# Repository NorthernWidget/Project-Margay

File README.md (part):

# Project-Margay

***Margay data logger v3.0.*** *Top side showing ATmega1284p processor, USB-C connector, screw terminal I/O on both sides, and LOG/STAT/RST buttons.*

Project Margay is a micro-scale environmental data logger based on the ALog series. It trades I/O capabilities for cost and size, resulting in a simple yet capable logger.

## Citation

If you use this data logger in a publication, please cite (temporary citation until a dedicated Margay paper is published):

**Wickert, A. D., K. R. Barnhart, W. H. Armstrong, M. Romero, B. Schulz, G.-H. C. Ng, C. T. Sandell, J. La Frenierre, S. B. Penprase, M. Van Wyk de Vries, and K. R. MacGregor (2024), [Automated ablation stakes to constrain temperature-index melt models](https://doi.org/10.1017/aog.2024.21), *Ann. Glaciol.*, *64*(92), 425–438, doi:10.1017/aog.2024.21.**

## Namesake

Due to its small size and adaptability to its environment, Project Margay owes its name to the small Margay cat native to the forests of Central and South America.

***A yawning margay cat***

## Technical Specifications

### Electronic Hardware
This includes a description of the PCB and component functionality

#### Features:
* ATMega1284p Processor
* 3.3v Logic
* On board full size SD card (for ease of field use)
* Extremely low sleep current
* Input voltage designed for use with easy to find alkaline batteries
* 0.1" Pitch headers can be populated with header pins and placed on a breadboard for prototyping

### Current iteration:

#### v3.0

***Margay data logger v3.0, back side.*** *Full-size SD card for data storage. US quarter (24.3 mm diameter) shown for scale.*

Changes from v2.2:
* USB-C connector (replacing micro-USB)
* Increased mounting hole sizes to fit #4 screws
* Moved one passive component to accommodate the larger holes

Input voltage: 3.5–5.5 V for regulated operation, 6.0 V absolute maximum; three alkaline AA or D cells (see [Battery voltage](#battery-voltage)). All other electrical specifications and pinout are identical to v2.2. Annotated pinout diagrams are in the [Pinout and board interfaces section below](#pinout-and-board-interfaces) and apply directly to v3.0.

### Past Iterations:

#### Features:
* ATMega644p Processor
* 3.3v Logic
* On board full size SD card (for ease of field use)
* Extremely low sleep current
* Input voltage designed for use with easy to find alkaline batteries
* 0.1" Pitch headers can be populated with header pins and placed on a breadboard for prototyping

#### v0.0 (Retired)
**Features** <br>
I<sub>Q</sub> = 1.6mA <br>
I<sub>out</sub> = 50mA, max (Regulated power supplied to sensors) <br>
V<sub>in</sub> = 3.3 ~ 5.5v <br>

**IO**:
* 1 I2C Bus
* 1 SPI Bus, with up to 2 CS pins
* 1 PWM Channel (output configurable to 3.3v or VBat via a jumper on bottom of board)
* RGB Status LED
* Auxiliary LED
* Reset Button
* Reconfigurable Button

#### v1.0
**Features** <br>
I<sub>Q</sub> = 2.5&mu;A <br>
I<sub>out</sub> = 50mA, max (Regulated power supplied to sensors) <br>
V<sub>in</sub> = 3.3 ~ 5.5v (Reverse polarity protected) <br>

**IO**
* 1 ADC, 18 bit
* 1 I<sup>2</sup>C Bus
* 1 SPI Bus, with up to 2 CS pins
* 1 PWM Channel (output configurable to 3.3v or VBat via a jumper on bottom of board)
* RGB Status LED
* Auxiliary LED
* Reset Button
* Reconfigurable Button

#### v2.0
**Features** <br>
I<sub>Q</sub> = <2.5&mu;A (Estimated) <br>
I<sub>out</sub> = 200mA, max (Regulated power supplied to sensors) <br>
V<sub>in</sub> = 3.3 ~ 5.5v (Reverse polarity protected) <br>

**IO**
* 1 ADC, 18 bit
* 1 I<sup>2</sup>C Bus
* 1 UART Channel
* 2 GPIO Pins (one configurable as an 8 bit ADC)
* 1 PWM Channel (output configurable to 3.3v or VBat via a jumper on bottom of board)
* RGB Status LED
* Auxiliary LED
* Reset Button
* Reconfigurable Button

#### v2.2
**Features** <br>
I<sub>Q</sub> = 1.68&mu;A <br>
I<sub>out</sub> = 200mA, max (Regulated power supplied to sensors) <br>
V<sub>in</sub> = 3.3 ~ 5.5v (Reverse polarity protected) <br>

**IO**
* 1 ADC, 18 bit
* 1 I<sup>2</sup>C Bus
* 1 UART Channel
* 2 GPIO Pins (one configurable as an 8 bit ADC)
* 1 PWM Channel (output configurable to 3.3v or VBat via a jumper on bottom of board)
* RGB Status LED
* Auxiliary LED
* Reset Button
* Reconfigurable Button

### Electronic Software and Firmware

* Programmable using the Arduino IDE https://www.arduino.cc/en/software
* Custom bootloader and board definition for ATMega1284p available via https://github.com/NorthernWidget/Arduino_Boards
* Custom libraries from Northern Widget and the open-source community
  * Primary data-logger functions
  * Libraries available with each sensor, exposing a standard interface
* Open-source licensing via GNU GPL 3.0

### Pinout and board interfaces
Pinout is listed on bottom of board. The pinout is identical across v2.2 and v3.0.

***Margay data logger with pins, connectors, and interactive items annotated, top side.***

**Pins are colored following this convention:**
* Ground: black
* Positive voltage: red
* Universal Serial Asynchronous Receiver--Transmitter (UART or USART) bus: blue
* Digital I/O: gray
* Analog measurement system: green
* I2C bus: purple

*The jumper on the front of the board, to the right of "B+" and "Ax", connects an on-board reference resistor (10 kOhm in our builds) with the analog pin Ax to create a voltage divider in which the sensor between Ax and REF is on the GND side of the voltage divider.*

***Margay data logger annotated, bottom side.*** This is where the labels for the above pins are printed.

In this pinout, the name of each pin is shown, as well as the group of pins which it belongs to, a detailed description of the pins and callouts follows:

#### Pins:
* 3v3, the switched 3.3v output rail, this rail can be turned on and off to disconnect power consumptive external devices
* GND, the main output ground
* BAT+, the positive connection for the battery line: 3.5–5.5 V for regulated operation, 6.0 V absolute maximum (see [Battery voltage](#battery-voltage) for the limits and the cells to use)
* BAT-, Negative battery connection, ***note: this pin is NOT interchangeable with GND, as BAT- is reverse voltage protected to prevent damage from plugging the battery in backwards***
* Vs, this is the switched PWM output, the voltage of this output is determined by a solder jumper on the bottom of the board, controlled by `VSwitch_Pin` - See information of limits and configuration below

* MOSI, this is the master out, slave in, pin for the SPI bus, which doubles as **D5** when SPI and SD card are not used
* MISO, this is the master in, slave out, pin for the SPI bus, which doubles as **D6** when SPI and SD card are not used
* SCK, this is the clock line for the SPI bus, which doubles as **D7** when SPI and SD card are not used
* CS, this is the chip select pin for the SPI bus, which doubles as both **D11** and **INT1** when external SPI is not used (Can be used even when SD card is used)

* SCL, this is the dedicated serial clock line for the I2C bus
* SDA, this is the dedicated serial data line for the I2C bus

#### Callouts:
1. This is the auxiliary LED, which indicate TX and RX status using red and blue channels, green channel is controlled by `BuiltInLED` pin
2. This is the USB connection (USB-C on v3.0; micro-USB on v2.x), which can be used for both programming via the Arduino IDE and serial monitoring
3. This is the primary RGB status LED, where the individual channels are controlled by **D15**, **D14**, and **D13**
4. This is the reconfigurable push-button, generally used to initiate logging, it is read by `LogInt` pin
5. This is the hardware reset button, which will force the micro to return to the initial state after code upload
6. This is the ICSP header, which can be used to burn the bootloader to the board or write programs to the chip without using the USB and bootloader

#### Onboard Pins:
Pin Name | Pin Number (v0.0) | Pin Number (v1.0) | Pin Number (v2.x) | Function
-------- | ----------------- | ----------------- | ----------------- | --------
`SD_CS` | D4 | D4 | D4 | Chip select pin on SD card
`SD_CD` | D1 | D1 | D1 | Card detection pin for SD card, active low, AUX power must be on to use
`BuiltInLED` | D19 | D20 | D20 | Connected to green channel on **AUX** LED, on when pin is low
`RedLED` | D13 | D13 | D13 | Connected to red channel on **STAT** LED, on when pin is low
`GreenLED` | D15 | D15 | D15 | Connected to green channel on **STAT** LED, on when pin is low
`BlueLED` | D14 | D14 | D14 | Connected to blue channel on **STAT** LED, on when pin is low
`VRef_Pin` | A2 | A2 | A3 | Analog pin to read 1.8v on board reference, AUX power must be on to use
`BatSensePin` | A0 | A0 | A2 | Analog pin to read battery voltage divider, AUX power must be on to use
`VSwitch_Pin` | D3 | D3 | D12 | Connected to MOSFET driver for **Vs** pin, active low
`Ext3v3Ctrl` | D12 | D19 | D22 | Turns on AUX power, active low
`I2C_SW` | N/A | D12 | D21 | Switches between on board I2C and external I2C
`PG` | D18 | D18 | D18 | Power good pin from core 3v3, can be used to test if core 3v3 is stable, pulled low when power is not stable
`ExtInt` | D11 | D11 | D11 | External interrupt and external chip select pin
`RTCInt` | D10 | D10 | D2 | Interrupt connected to RTC /INT line, active low
`LogInt` | D2 | D2 | A4 | Interrupt connected to **LOG** button, active low

#### VSwitch Power Limits/Configuration:
Jumper Selected | Logger Power Source | Current Limit, Avg [mA] | Power Limit, Avg [W] | Set by
--------------- | ------------------- | ---------------------- | -------------------- | ------
VMain | USB | 100 | 0.5 | TPS2104, USB input (IN2)<sup>1</sup>
VMain | Bat | 500 | 2.25 | TPS2104, battery input (IN1)
3v3 | USB | 100 | 0.33 | TPS2104, USB input (IN2)<sup>1</sup>
3v3 | Bat | 200 | 0.66 | TPS7A05, shared with the SD card and on-board sensors

<sup>1</sup> <small>Rated continuous current. The TPS2104 can deliver up to 220 mA here, with a larger voltage drop.</small>

Note: Instantaneous current may exceed these values — these values correspond to the time-averaged power consumption. This distinction is most important when driving a load via PWM.

#### Battery voltage

Use three alkaline cells in series, AA or D. A fresh pack reads about 4.8 V (1.56–1.65 V per cell) and runs the logger for the life of the cells.

| Limit | Voltage | Set by |
|---|---|---|
| Absolute maximum | 6.0 V | every chip on the battery line: TPS79733 (core regulator), TPS22916 (battery switch), TPS2104 (USB/battery switch), TPS7A05 (switched 3.3 V regulator) and MIC94090 (Vs switch, with the jumper on its default side) |
| Maximum for operation | 5.5 V | the same chips |
| Core 3.3 V in regulation down to | 3.5 V | the TPS79733's dropout (200 mV maximum at 10 mA) |
| Switched 3.3 V in regulation at its full 200 mA down to | 3.63 V | the TPS7A05's dropout plus the switches ahead of it |

Below these, the 3.3 V rails follow the battery down. The logger reports a battery under 3.3 V as too low to work properly (red, fast blinking).

Do not use:
* **Lithium AA cells** (lithium iron disulfide, such as Energizer Ultimate Lithium). Three fresh cells read 5.37–5.49 V, within 0.13 V of the 5.5 V maximum.
* **3.6 V lithium AA-size cells** (lithium thionyl chloride, such as Saft LS14500). Three in series reach about 11 V and will destroy the logger.

NiMH cells (about 3.75–4.26 V for three) work, but leave only about 0.1 V of headroom for the switched 3.3 V rail at full load.

On USB, use a standard 5 V port or charger. The FT231X USB chip sets the ceiling there: its absolute maximum is 5.5 V, behind one Schottky diode.

## On-board Devices

### I2C

| **Device**                                                	| **Default address** 	| **Reprogrammable address** 	| **Function**                                                     	|
|-----------------------------------------------------------	|---------------------	|----------------------------	|------------------------------------------------------------------	|
| [DS3231](https://github.com/NorthernWidget/DS3231_Logger) 	| 0x68                	| N                          	| Real-time clock                                                  	|
| [MCP3421](https://github.com/NorthernWidget/MCP3421)      	| 0x6A                	| N                          	| ADC                                                              	|
| [BME280](https://github.com/NorthernWidget/BME_Library)   	| 0x77                	| N                          	| On-board barometric pressure, temperature, and relative humidity 	|

### SPI

* SD Card

### UART (USART)

* FTDI USB-Serial converter

## Assembly

Assembling this data logger is possible by hand with sufficient skill and the following tools:
* Temperature-controlled soldering iron
* Hot-air rework station
* Equipment for stenciling with solder paste
* ESD-safe tweezers and workstation
* Solder wick

Mechanized assembly by a professional circuit-board assembly house, which is available in many parts of the world, may be preferred due to the complexity of this data logger board.

## Programming

### Downloading and installing the Arduino IDE

Go to https://www.arduino.cc/en/software and download the IDE for your operating system. The web editor does not support custom libraries and will not work for this project. Install the IDE and open it before continuing.

For additional setup guidance, see the [Northern Widget tutorial](https://docs.northernwidget.com/tutorial/).

### Installing the bootloader

Before a data logger can receive programs via USB, it must have a *bootloader* installed. You can read more about bootloaders here: https://www.arduino.cc/en/Hacking/Bootloader.

The bootloader is loaded via the 6-pin ICSP (ISP) header using an in-circuit system programmer. Many programmers work:
* The official [AVR ISP mkII](http://ww1.microchip.com/downloads/en/DeviceDoc/Atmel-42093-AVR-ISP-mkII_UserGuide.pdf) (no longer produced but available used)
* Using an [Arduino as an ISP](https://www.arduino.cc/en/tutorial/arduinoISP)
* The versatile [Olimex AVR-ISP-MK2](https://www.olimex.com/Products/AVR/Programmers/AVR-ISP-MK2/open-source-hardware)
* The [Adafruit USBtinyISP](https://www.adafruit.com/product/46)

***Important note for Linux users:*** You must supply permissions to the Arduino IDE for it to use the ICSP, or run the IDE with `sudo`.

To install the bootloader:

1. Open the Arduino IDE and install the Northern Widget board definitions: https://github.com/NorthernWidget/Arduino_Boards — the Margay uses the **TLog v1** definition.
2. Select ***ATMega1284p 8MHz*** under *Tools → Board → Northern Widget Boards*.
3. Plug the Margay into your computer via USB (USB-C on v3.0; micro-USB on v2.x) to power it.
4. Plug your ISP into your computer and onto the 6-pin ICSP header. The ribbon cable should face away from the board; if programming fails, try flipping the connector.
5. Go to *Tools → Programmer* and select your programmer.
6. Go to *Tools → Burn Bootloader*. Within a few seconds you will see a success or failure message.

***Note: Download and install drivers for your ISP before use.***

### Hardware test sketch

The [`MargaySetup`](Software/MargaySetup/MargaySetup.ino) sketch verifies every hardware subsystem over the serial monitor at 38400 baud. It also handles serial number programming (`SN Set` / `SN Read`). See the [Full hardware test command reference](#full-hardware-test-command-reference) table below.

Install these libraries before uploading (see [Arduino manual install guide](https://www.arduino.cc/en/Guide/Libraries)):
* [DS3231](https://github.com/NorthernWidget/DS3231) — real-time clock
* [MCP3421](https://github.com/NorthernWidget/MCP3421) — on-board ADC
* SD — bundled with the Arduino IDE

### Data logging

For data logging, use the [Margay_Library](https://github.com/NorthernWidget/Margay_Library). It manages sleep/wake, SD writes, RTC reads, and on-board sensor sampling automatically. See the [Sample code](#sample-code) section below.

Install these libraries manually from GitHub (see [Arduino manual install guide](https://www.arduino.cc/en/Guide/Libraries)):
* [Margay_Library](https://github.com/NorthernWidget/Margay_Library)
* [DS3231_Logger](https://github.com/NorthernWidget/DS3231_Logger)
* [NW_MCP3421](https://github.com/NorthernWidget/MCP3421)
* [BME](https://github.com/NorthernWidget/BME_Library)
* [SdFat](https://github.com/greiman/SdFat) — available via *Tools → Manage Libraries*

### Setting the serial number

Upload the [MargaySetup](Software/MargaySetup/MargaySetup.ino) sketch, open the serial monitor at **38400 baud**, and type `SN Set` followed by a carriage return or newline. You will be prompted for three 4-digit hexadecimal fields:
* **Board type:** `0x4D03` for Margay v3.0; `0x4D02` for v2.2 (full series: v0.0 = `0x4D00`, v1.0 = `0x4D01`). If you built your own board, do not use these codes — they are reserved for Northern Widget recordkeeping.
* **Group ID:** Used to denote collaborative projects vs. internal use vs. general sales.
* **Unique ID:** A monotonically increasing number.

To read back the serial number, type `SN Read`.

### Full hardware test command reference

The same sketch provides a serial command interface at **38400 baud** for testing all individual hardware subsystems. Send a command followed by a carriage return or newline. Continuous tests run until a carriage return is sent to stop them.

Command | Description
--------|------------
`SD` | Writes a random value and short string to the SD card, reads it back, reports PASS/FAIL
`Clock` | Sets the RTC to a known time, waits 5 seconds, reads it back, reports PASS/FAIL
`I2C` | Scans the I2C bus and prints the address of every device found
`ADC Disp` | Continuously prints voltages for the on-board reference, thermistor, battery, and external ADC (Ax)
`IO` | Toggles the VSwitch and ExtInt pins
`PG` | Reads the Power Good pin and reports PASS/FAIL
`Power` | Toggles the external 3.3V rail on and off
`Button` | Waits 2 seconds for the Log button to be pressed and reports if detected
`LED` | Cycles through each channel of the RGB and AUX LEDs
`SN Set` | Sets the serial number in EEPROM (see above)
`SN Read` | Reads back the serial number from EEPROM

### Using Custom Software (Developer)
As we provide all information about on board pins and their functionality, it is easy for a user to write their own code in the Arduino IDE to leverage the hardware capabilities of the Margay to whatever degree is desired. To do this, the Northern Widget board file can be used (as described above), or the **[MightyCore](https://github.com/MCUdude/MightyCore)** board files can be used. These are the board files the Northern Widget ones were based on, but allow for more compilation options for the user. Full instructions for installation and use are provided on the MightyCore GitHub page.

For **v2.0 and later** (ATmega1284p), the recommended settings are:

Setting | Value
--------|------
`Board` | `ATmega1284`
`Pinout` | `Standard`
`Clock` | `8MHz External`
`Compiler LTO` | `Disabled`
`Variant` | `1284P`
`BOD` | `2.7v`

For **v0.0 and v1.0** (ATmega644p), the recommended settings are:

Setting | Value
--------|------
`Board` | `ATmega644`
`Pinout` | `Standard`
`Clock` | `8MHz External`
`Compiler LTO` | `Disabled`
`Variant` | `644P / 644PA`
`BOD` | `2.7v`

#### Sample code

`Margay_NoSensors.ino`

```c++
#include "Margay.h"
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
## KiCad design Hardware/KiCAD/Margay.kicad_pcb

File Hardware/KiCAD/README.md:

# Hardware/Margay_2 — Eagle-to-KiCAD port, current working version (work in progress)

This is the most current KiCAD design for the Margay v3.0, representing the active Eagle-to-KiCAD port.

**Current state:** schematic is split across three hierarchical sheets (`Margay_1/2/3.kicad_sch`) imported from Eagle; every symbol and footprint now comes from the shared `nw-cold-silicon` library, and the importer's `Margay-eagle-import.kicad_sym` and `Margay.pretty` have been retired. PCB layout (`Margay.kicad_pcb`) is also present. Both are works in progress and have not been verified against the v3.0 production Gerbers.

Tracking issue: https://github.com/NorthernWidget/Project-Margay/issues/41

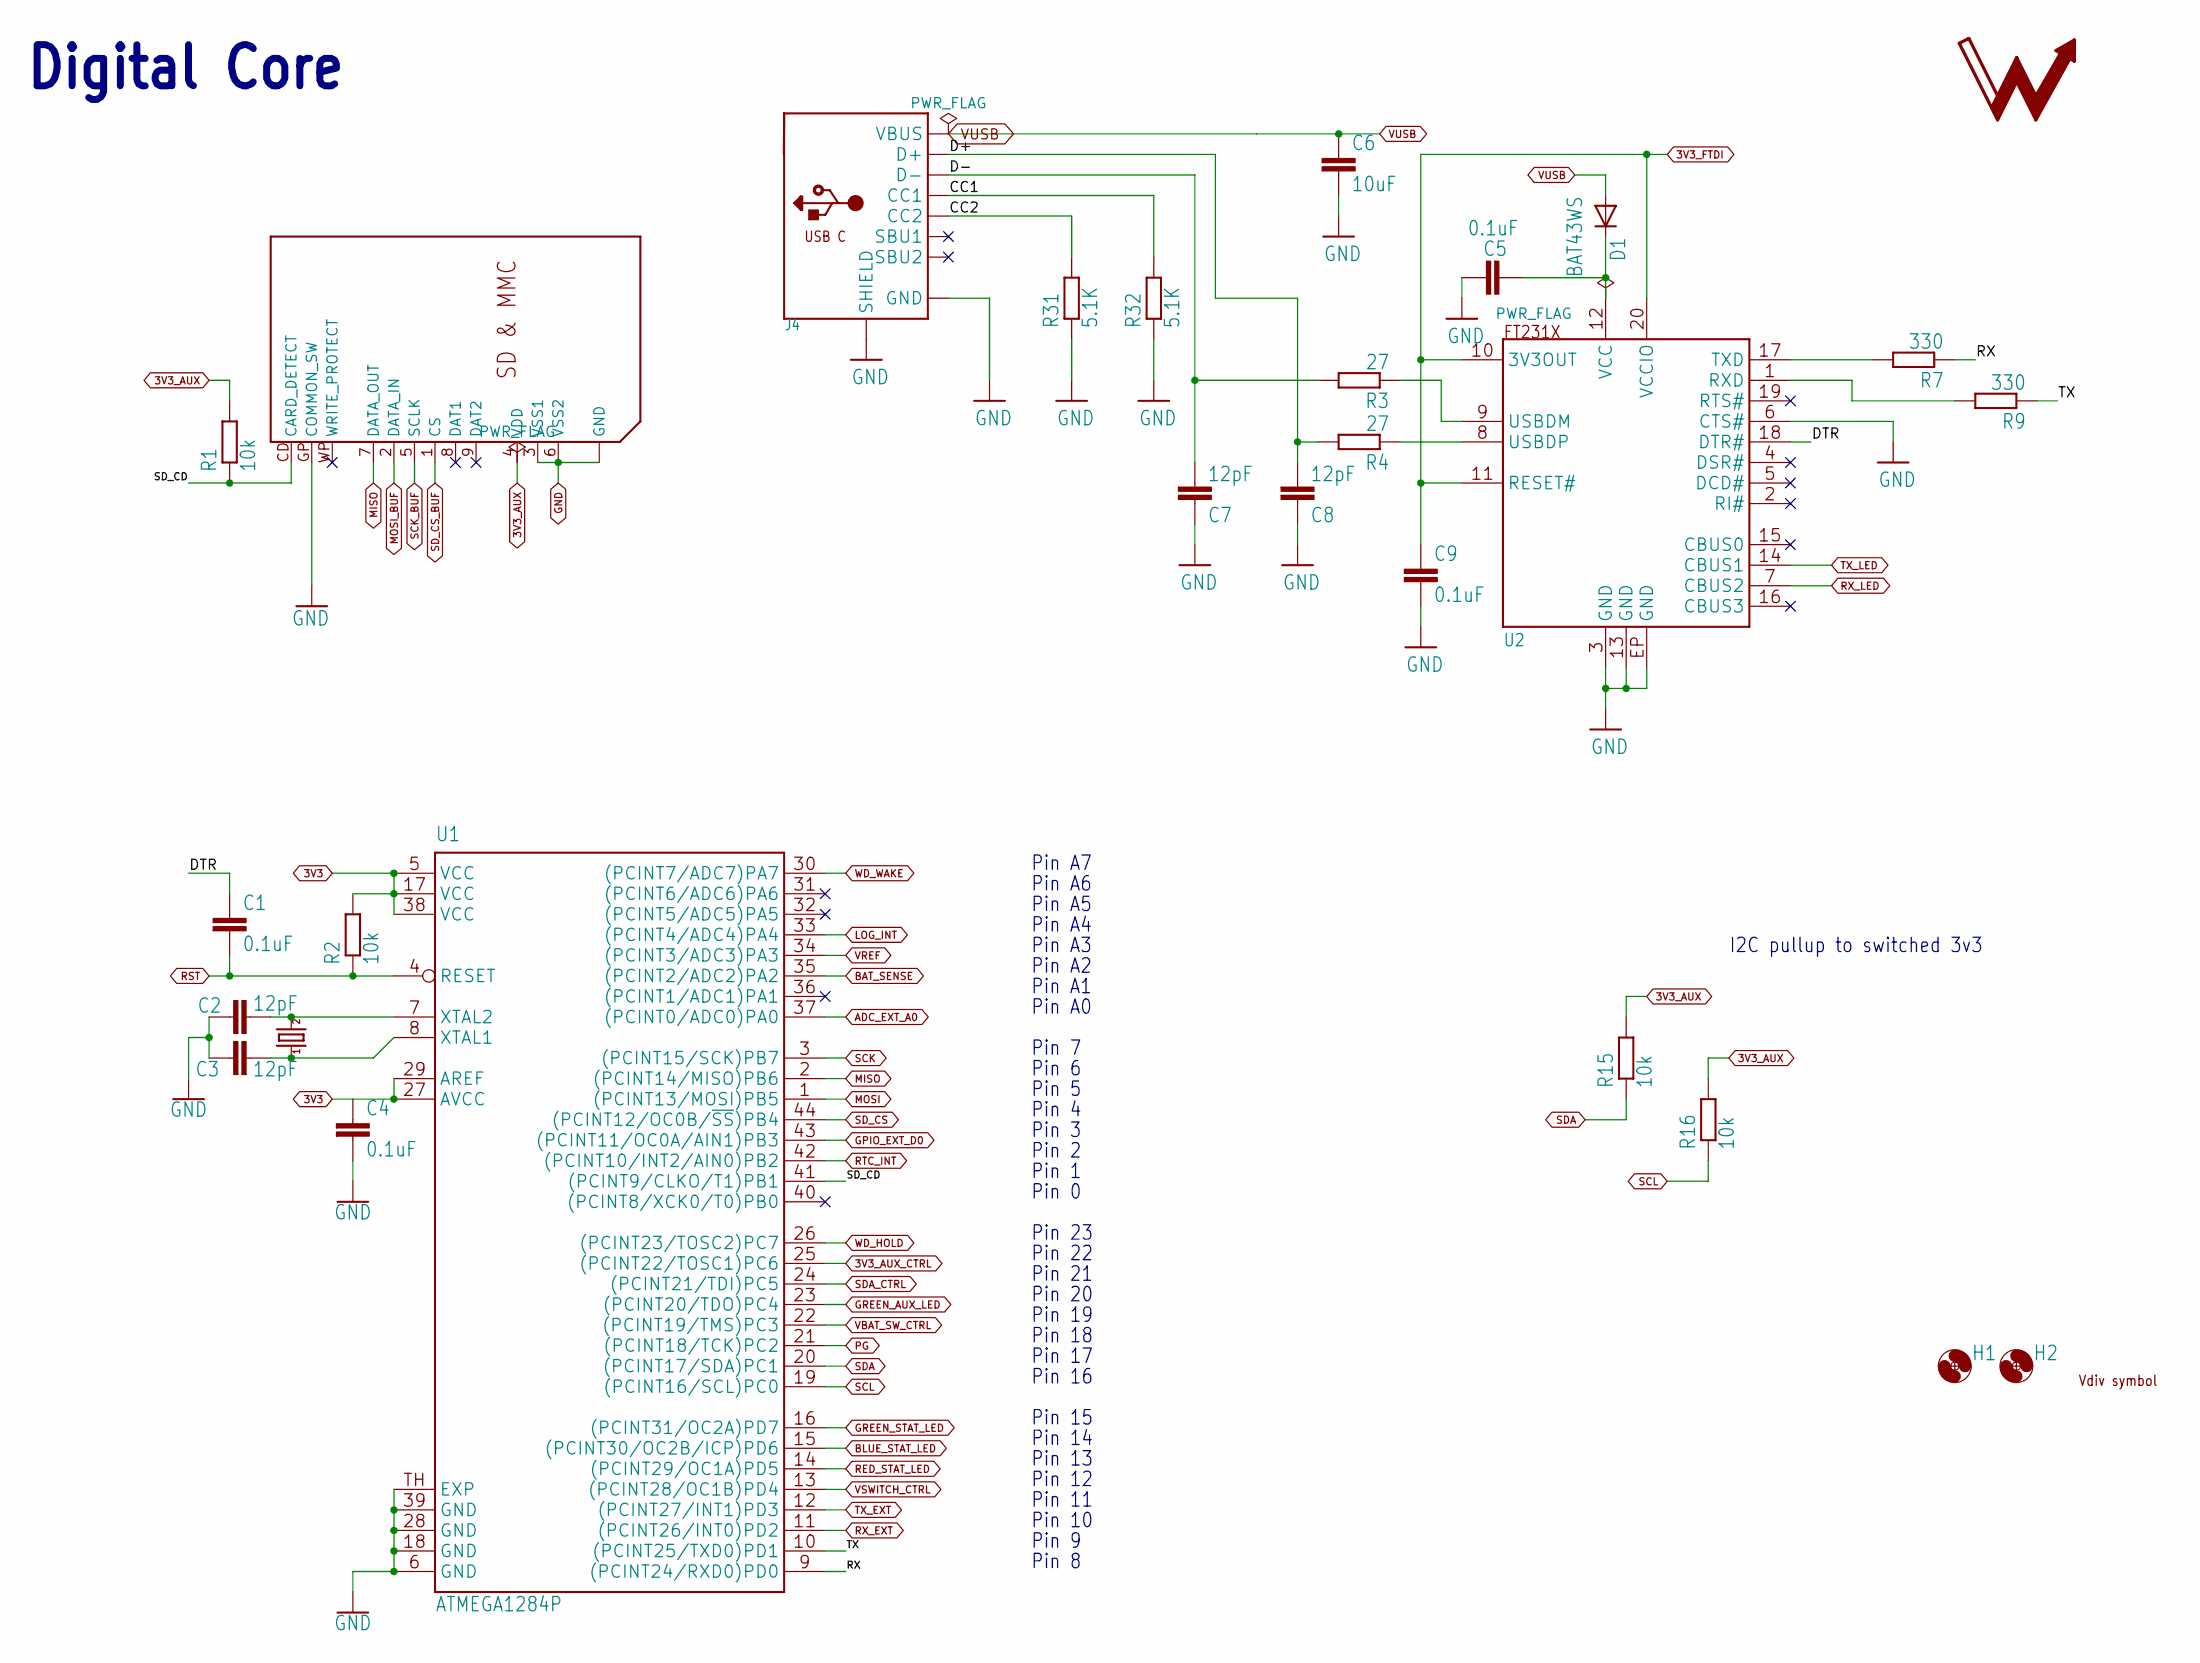
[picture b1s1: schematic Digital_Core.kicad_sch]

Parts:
C1, C4, C5, C9: 0.1uF; C0402; MPN GCM155R71C104KA55D; DIGIKEY 490-4759-1-ND
C2, C3, C7, C8: 12pF; C0402; MPN CGA2B2C0G1H120J050BA; DIGIKEY 445-5585-1-ND
C6: 10uF; C0805; MPN GRM21BR61C106KE15K; DIGIKEY 490-6473-1-ND
D1: BAT43WS; SOD323-R; MPN BAT43WS-HE3_A-08; DIGIKEY 112-BAT43WS-HE3_A-08CT-ND
H1, H2: MOUNTING_HOLE4_NP_CLOSE; 4_40_CLOSE; MPN N/A; DIGIKEY DNP
J1: SDMMCWR-CRD; SD_WURTH_WR-CRD; MPN 693063010911; DIGIKEY 732-3817-1-ND
J4: USB_C; USB_C_CUSB31-CFM2AX-01-X; MPN USB4105-GF-A; DIGIKEY 2073-USB4105-GF-ACT-ND
LOGO1: NWLOGO_MED
R1, R2, R15, R16: 10k; R0402; MPN ERJ-2RKF1002X; DIGIKEY P10.0KLCT-ND
R3, R4: 27; R0402; MPN ERJ-2RKF27R0X; DIGIKEY P27.0LCT-ND
R7, R9: 330; R0402; MPN ERJ-2RKF3300X; DIGIKEY P330LCT-ND
R31, R32: 5.1K; R0402; MPN ERJ-2RKF5101X; DIGIKEY P5.10KLCT-ND
U1: ATMEGA1284P; MLF44-TH; MPN ATMEGA1284P-MU; DIGIKEY ATMEGA1284P-MU-ND
U2: FT231X-Q; QFN20; MPN FT231XQ-R; DIGIKEY 768-1128-1-ND
U$1: VDIV_MARGAYFULL-VDIV; VDIV_MARGAY_2026; MPN N/A; DIGIKEY DNP
XTAL1: CRYSTAL5X3.2; CRYSTAL_5X3.2_2-SMD; MPN ECS-80-12-30-JGN-TR; DIGIKEY 50-ECS-80-12-30-JGN-CT-ND

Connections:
3V3: C4.1, R2.2, U1.5 (VCC), U1.17 (VCC), U1.27 (AVCC), U1.29 (AREF), U1.38 (VCC); also elsewhere on the board
3V3_AUX: J1.4 (VDD), R1.2, R15.2, R16.2; also elsewhere on the board
3V3_AUX_CTRL: U1.25 ((PCINT22/TOSC1)PC6); also elsewhere on the board
3V3_FTDI: C9.1, U2.10 (3V3OUT), U2.11 (RESET#), U2.20 (VCCIO); also elsewhere on the board
/Digital_Core/CC1: J4.A5 (CC1), R32.2
/Digital_Core/CC2: J4.B5 (CC2), R31.2
/Digital_Core/D+: C8.2, J4.A6 (D+), J4.B6 (D+), R4.2
/Digital_Core/D-: C7.2, J4.A7 (D-), J4.B7 (D-), R3.2
/Digital_Core/DTR: C1.1, U2.18 (DTR#)
/Digital_Core/RX: R7.1, U1.9 ((PCINT24/RXD0)PD0)
/Digital_Core/SD_CD: J1.CD (CARD_DETECT), R1.1, U1.41 ((PCINT9/CLKO/T1)PB1)
/Digital_Core/TX: R9.1, U1.10 ((PCINT25/TXD0)PD1)
ADC_EXT_A0: U1.37 ((PCINT0/ADC0)PA0); also elsewhere on the board
BAT_SENSE: U1.35 ((PCINT2/ADC2)PA2); also elsewhere on the board
BLUE_STAT_LED: U1.15 ((PCINT30/OC2B/ICP)PD6); also elsewhere on the board
GND: C2.1, C3.1, C4.2, C5.2, C6.2, C7.1, C8.1, C9.2, J1.3 (VSS1), J1.6 (VSS2), J1.GP (COMMON_SW), J1.GP2 (GND), J1.GP3 (GND), J1.GP4 (GND), J4.A1B12 (GND), J4.B1A12 (GND), J4.S1 (SHIELD), R31.1, R32.1, U1.6 (GND), U1.18 (GND), U1.28 (GND), U1.39 (GND), U1.TH (EXP), U2.3 (GND), U2.6 (CTS#), U2.13 (GND), U2.EP (GND); also elsewhere on the board
GPIO_EXT_D0: U1.43 ((PCINT11/OC0A/AIN1)PB3); also elsewhere on the board
GREEN_AUX_LED: U1.23 ((PCINT20/TDO)PC4); also elsewhere on the board
GREEN_STAT_LED: U1.16 ((PCINT31/OC2A)PD7); also elsewhere on the board
LOG_INT: U1.33 ((PCINT4/ADC4)PA4); also elsewhere on the board
MISO: J1.7 (DATA_OUT), U1.2 ((PCINT14/MISO)PB6); also elsewhere on the board
MOSI: U1.1 ((PCINT13/MOSI)PB5); also elsewhere on the board
MOSI_BUF: J1.2 (DATA_IN); also elsewhere on the board
unnamed: C3.2, U1.8 (XTAL1), XTAL1.OSC1 (1)
unnamed: C2.2, U1.7 (XTAL2), XTAL1.OSC2 (2)
unnamed: R9.2, U2.1 (RXD)
unnamed: R7.2, U2.17 (TXD)
unnamed: R3.1, U2.9 (USBDM)
unnamed: R4.1, U2.8 (USBDP)
PG: U1.21 ((PCINT18/TCK)PC2); also elsewhere on the board
RED_STAT_LED: U1.14 ((PCINT29/OC1A)PD5); also elsewhere on the board
RST: C1.2, R2.1, U1.4 (RESET); also elsewhere on the board
RTC_INT: U1.42 ((PCINT10/INT2/AIN0)PB2); also elsewhere on the board
RX_EXT: U1.11 ((PCINT26/INT0)PD2); also elsewhere on the board
RX_LED: U2.7 (CBUS2); also elsewhere on the board
SCK: U1.3 ((PCINT15/SCK)PB7); also elsewhere on the board
SCK_BUF: J1.5 (SCLK); also elsewhere on the board
SCL: R16.1, U1.19 ((PCINT16/SCL)PC0); also elsewhere on the board
SDA: R15.1, U1.20 ((PCINT17/SDA)PC1); also elsewhere on the board
SDA_CTRL: U1.24 ((PCINT21/TDI)PC5); also elsewhere on the board
SD_CS: U1.44 ((PCINT12/OC0B/~SS)PB4); also elsewhere on the board
SD_CS_BUF: J1.1 (CS); also elsewhere on the board
TX_EXT: U1.12 ((PCINT27/INT1)PD3); also elsewhere on the board
TX_LED: U2.14 (CBUS1); also elsewhere on the board
VBAT_SW_CTRL: U1.22 ((PCINT19/TMS)PC3); also elsewhere on the board
VREF: U1.34 ((PCINT3/ADC3)PA3); also elsewhere on the board
VSWITCH_CTRL: U1.13 ((PCINT28/OC1B)PD4); also elsewhere on the board
WD_HOLD: U1.26 ((PCINT23/TOSC2)PC7); also elsewhere on the board

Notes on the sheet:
Pin A2
Pin 13
Pin 23
Pin A7
Pin 20
Pin 6
Pin 16
Pin 17
Pin 5
Pin 12
Pin 14
Pin 9
Pin 0
Pin 4
Pin 10
Pin 22
Pin 8
Pin A6
Pin 7
Pin A4
Pin 15
Digital Core
Pin 3
Pin A1
Pin 18
Pin A0
Pin 19
Pin 1
Pin 21
I2C pullup to switched 3v3
Pin A3
Pin A5
Pin 11
Pin 2

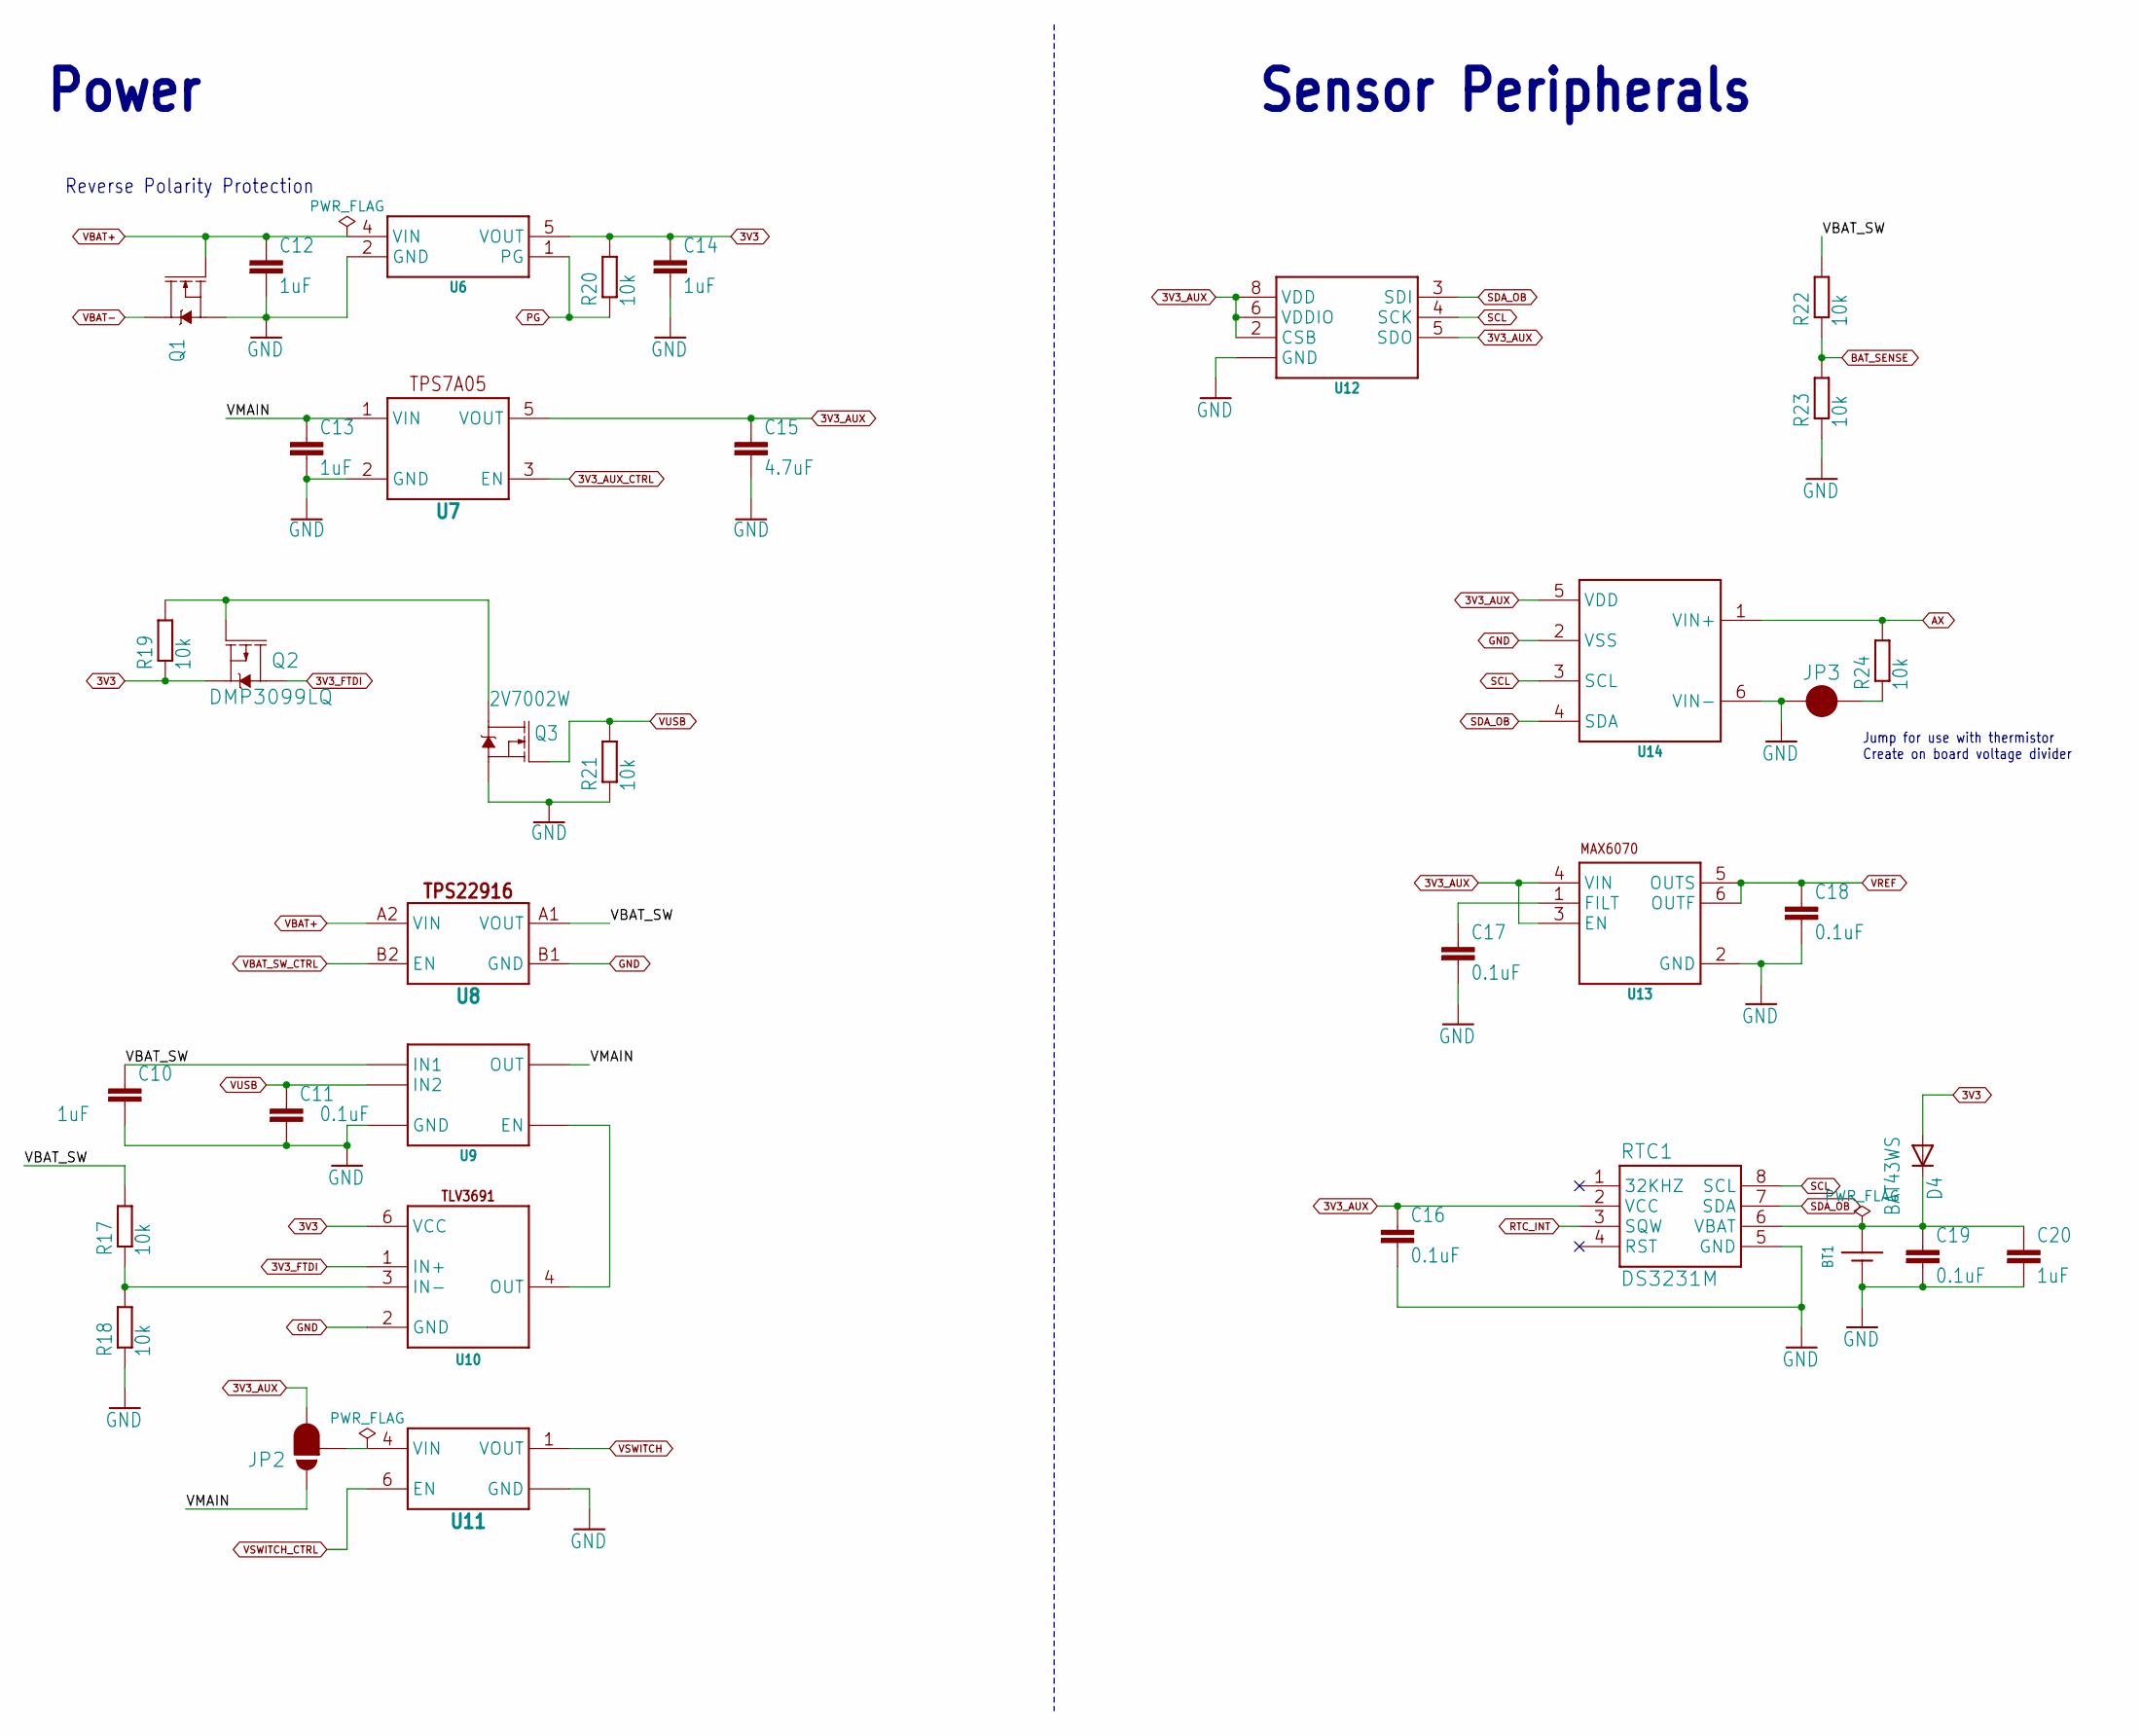
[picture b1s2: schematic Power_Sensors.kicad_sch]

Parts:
BT1: BATTERY_COIN12MM; LINX_BAT-HLD-012-SMT; MPN BK-916-TR; DIGIKEY BK-916-CT-ND
C10, C12, C13, C14, C20: 1uF; C0603; MPN GCM188R71E105KA64D; DIGIKEY 490-10673-1-ND
C11, C16, C17, C18, C19: 0.1uF; C0402; MPN GCM155R71C104KA55D; DIGIKEY 490-4759-1-ND
C15: 4.7uF; C0603; MPN GRT188R61C475KE13J; DIGIKEY 490-GRT188R61C475KE13JCT-ND
D4: BAT43WS; SOD323-R; MPN BAT43WS-HE3_A-08; DIGIKEY 112-BAT43WS-HE3_A-08CT-ND
JP2: JUMPER-SMT_3_1-NC_PASTE_SILK; SMT-JUMPER_3_1-NC_PASTE_SILK; MPN N/A; DIGIKEY DNP
JP3: JUMPER-SMT_2_NC_PASTE_SILK; SMT-JUMPER_2_NC_PASTE_SILK; MPN N/A; DIGIKEY DNP
Q1: MOSFET-NCH-DMG3404L; SOT23-3; MPN DMG3404L-7; DIGIKEY DMG3404L-7DICT-ND
Q2: DMP3099LQ; SOT23-3; MPN DMP3099LQ-7; DIGIKEY 31-DMP3099LQ-7CT-ND
Q3: 2V7002W; SOT323; MPN 2V7002WT1G; DIGIKEY 2V7002WT1GOSCT-ND
R17, R18, R19, R20, R21: 10k; R0402; MPN ERJ-2RKF1002X; DIGIKEY P10.0KLCT-ND
R22, R23, R24: 10k; R0603; MPN RG1608P-103-B-T5; DIGIKEY RG16P10.0KBCT-ND
RTC1: DS3231M; SO08; MPN DS3231MZ+; DIGIKEY DS3231MZ+-ND
U6: TPS797; DCK_R-PDSO-G5; MPN TPS79733DCKR; DIGIKEY 296-11990-1-ND
U7: TPS7A05DBV; SOT23-5; MPN TPS7A0533PDBVR; DIGIKEY 296-TPS7A0533PDBVRCT-ND
U8: TPS22916YFP; YFP0004; MPN TPS22916CYFPT; DIGIKEY 296-47464-1-ND
U9: TPS210; SOT23-5; MPN TPS2104DBVT; DIGIKEY 296-TPS2104DBVTCT-ND
U10: TLV3691DPF; DPF0006A; MPN TLV3691IDPFR; DIGIKEY 296-37242-6-ND
U11: MIC9409C6; SC-70_6; MPN MIC94090YC6-TR; DIGIKEY 576-3484-1-ND
U12: BME280; MPN BME280; DIGIKEY 828-1063-1-ND
U13: MAX6070BAUT18; SOT23-6L; MPN MAX6070BAUT18+T; DIGIKEY MAX6070BAUT18+TCT-ND
U14: MCP342; SOT23-6L; MPN MCP3421A1T-E/CH; DIGIKEY MCP3421A1T-E/CHCT-ND

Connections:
3V3: C14.1, D4.A, Q2.2 (S), R19.1, R20.2, U6.5 (VOUT), U10.6 (VCC); also elsewhere on the board
3V3_AUX: C15.1, C16.1, JP2.3, RTC1.2 (VCC), U7.5 (VOUT), U12.2 (CSB), U12.5 (SDO), U12.6 (VDDIO), U12.8 (VDD), U13.3 (EN), U13.4 (VIN), U14.5 (VDD); also elsewhere on the board
3V3_AUX_CTRL: U7.3 (EN); also elsewhere on the board
3V3_FTDI: Q2.3 (D), U10.1 (IN+); also elsewhere on the board
/Power_Sensors/VBAT_SW: C10.1, R17.2, R22.2, U8.A1 (VOUT), U9.5 (IN1)
/Power_Sensors/VMAIN: C13.1, JP2.1, U7.1 (VIN), U9.4 (OUT)
AX: R24.2, U14.1 (VIN+); also elsewhere on the board
BAT_SENSE: R22.1, R23.2; also elsewhere on the board
GND: BT1.GND (-), C10.2, C11.2, C12.2, C13.2, C14.2, C15.2, C16.2, C17.2, C18.2, C19.2, C20.2, JP3.1, Q1.2 (S), Q3.2 (S), R18.1, R21.1, R23.1, RTC1.5 (GND), U6.2 (GND), U7.2 (GND), U8.B1 (GND), U9.2 (GND), U10.2 (GND), U11.2 (GND), U11.5 (GND), U12.1 (GND), U12.7 (GND), U13.2 (GND), U14.2 (VSS), U14.6 (VIN-); also elsewhere on the board
unnamed: BT1.POWER0 (+), C19.1, C20.1, D4.C, RTC1.6 (VBAT)
unnamed: JP3.2, R24.1
unnamed: Q2.1 (G), Q3.3 (D), R19.2
unnamed: R17.1, R18.2, U10.3 (IN-)
unnamed: U9.1 (EN), U10.4 (OUT)
unnamed: JP2.2, U11.4 (VIN)
unnamed: C17.1, U13.1 (FILT)
PG: R20.1, U6.1 (PG); also elsewhere on the board
RTC_INT: RTC1.3 (SQW); also elsewhere on the board
SCL: RTC1.8 (SCL), U12.4 (SCK), U14.3 (SCL); also elsewhere on the board
SDA_OB: RTC1.7 (SDA), U12.3 (SDI), U14.4 (SDA); also elsewhere on the board
VBAT+: C12.1, Q1.1 (G), U6.4 (VIN), U8.A2 (VIN); also elsewhere on the board
VBAT-: Q1.3 (D); also elsewhere on the board
VBAT_SW_CTRL: U8.B2 (EN); also elsewhere on the board
VREF: C18.1, U13.5 (OUTS), U13.6 (OUTF); also elsewhere on the board
VSWITCH: U11.1 (VOUT); also elsewhere on the board
VSWITCH_CTRL: U11.6 (EN); also elsewhere on the board

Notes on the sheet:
Jump for use with thermistor Create on board voltage divider
Power
Reverse Polarity Protection
Sensor Peripherals

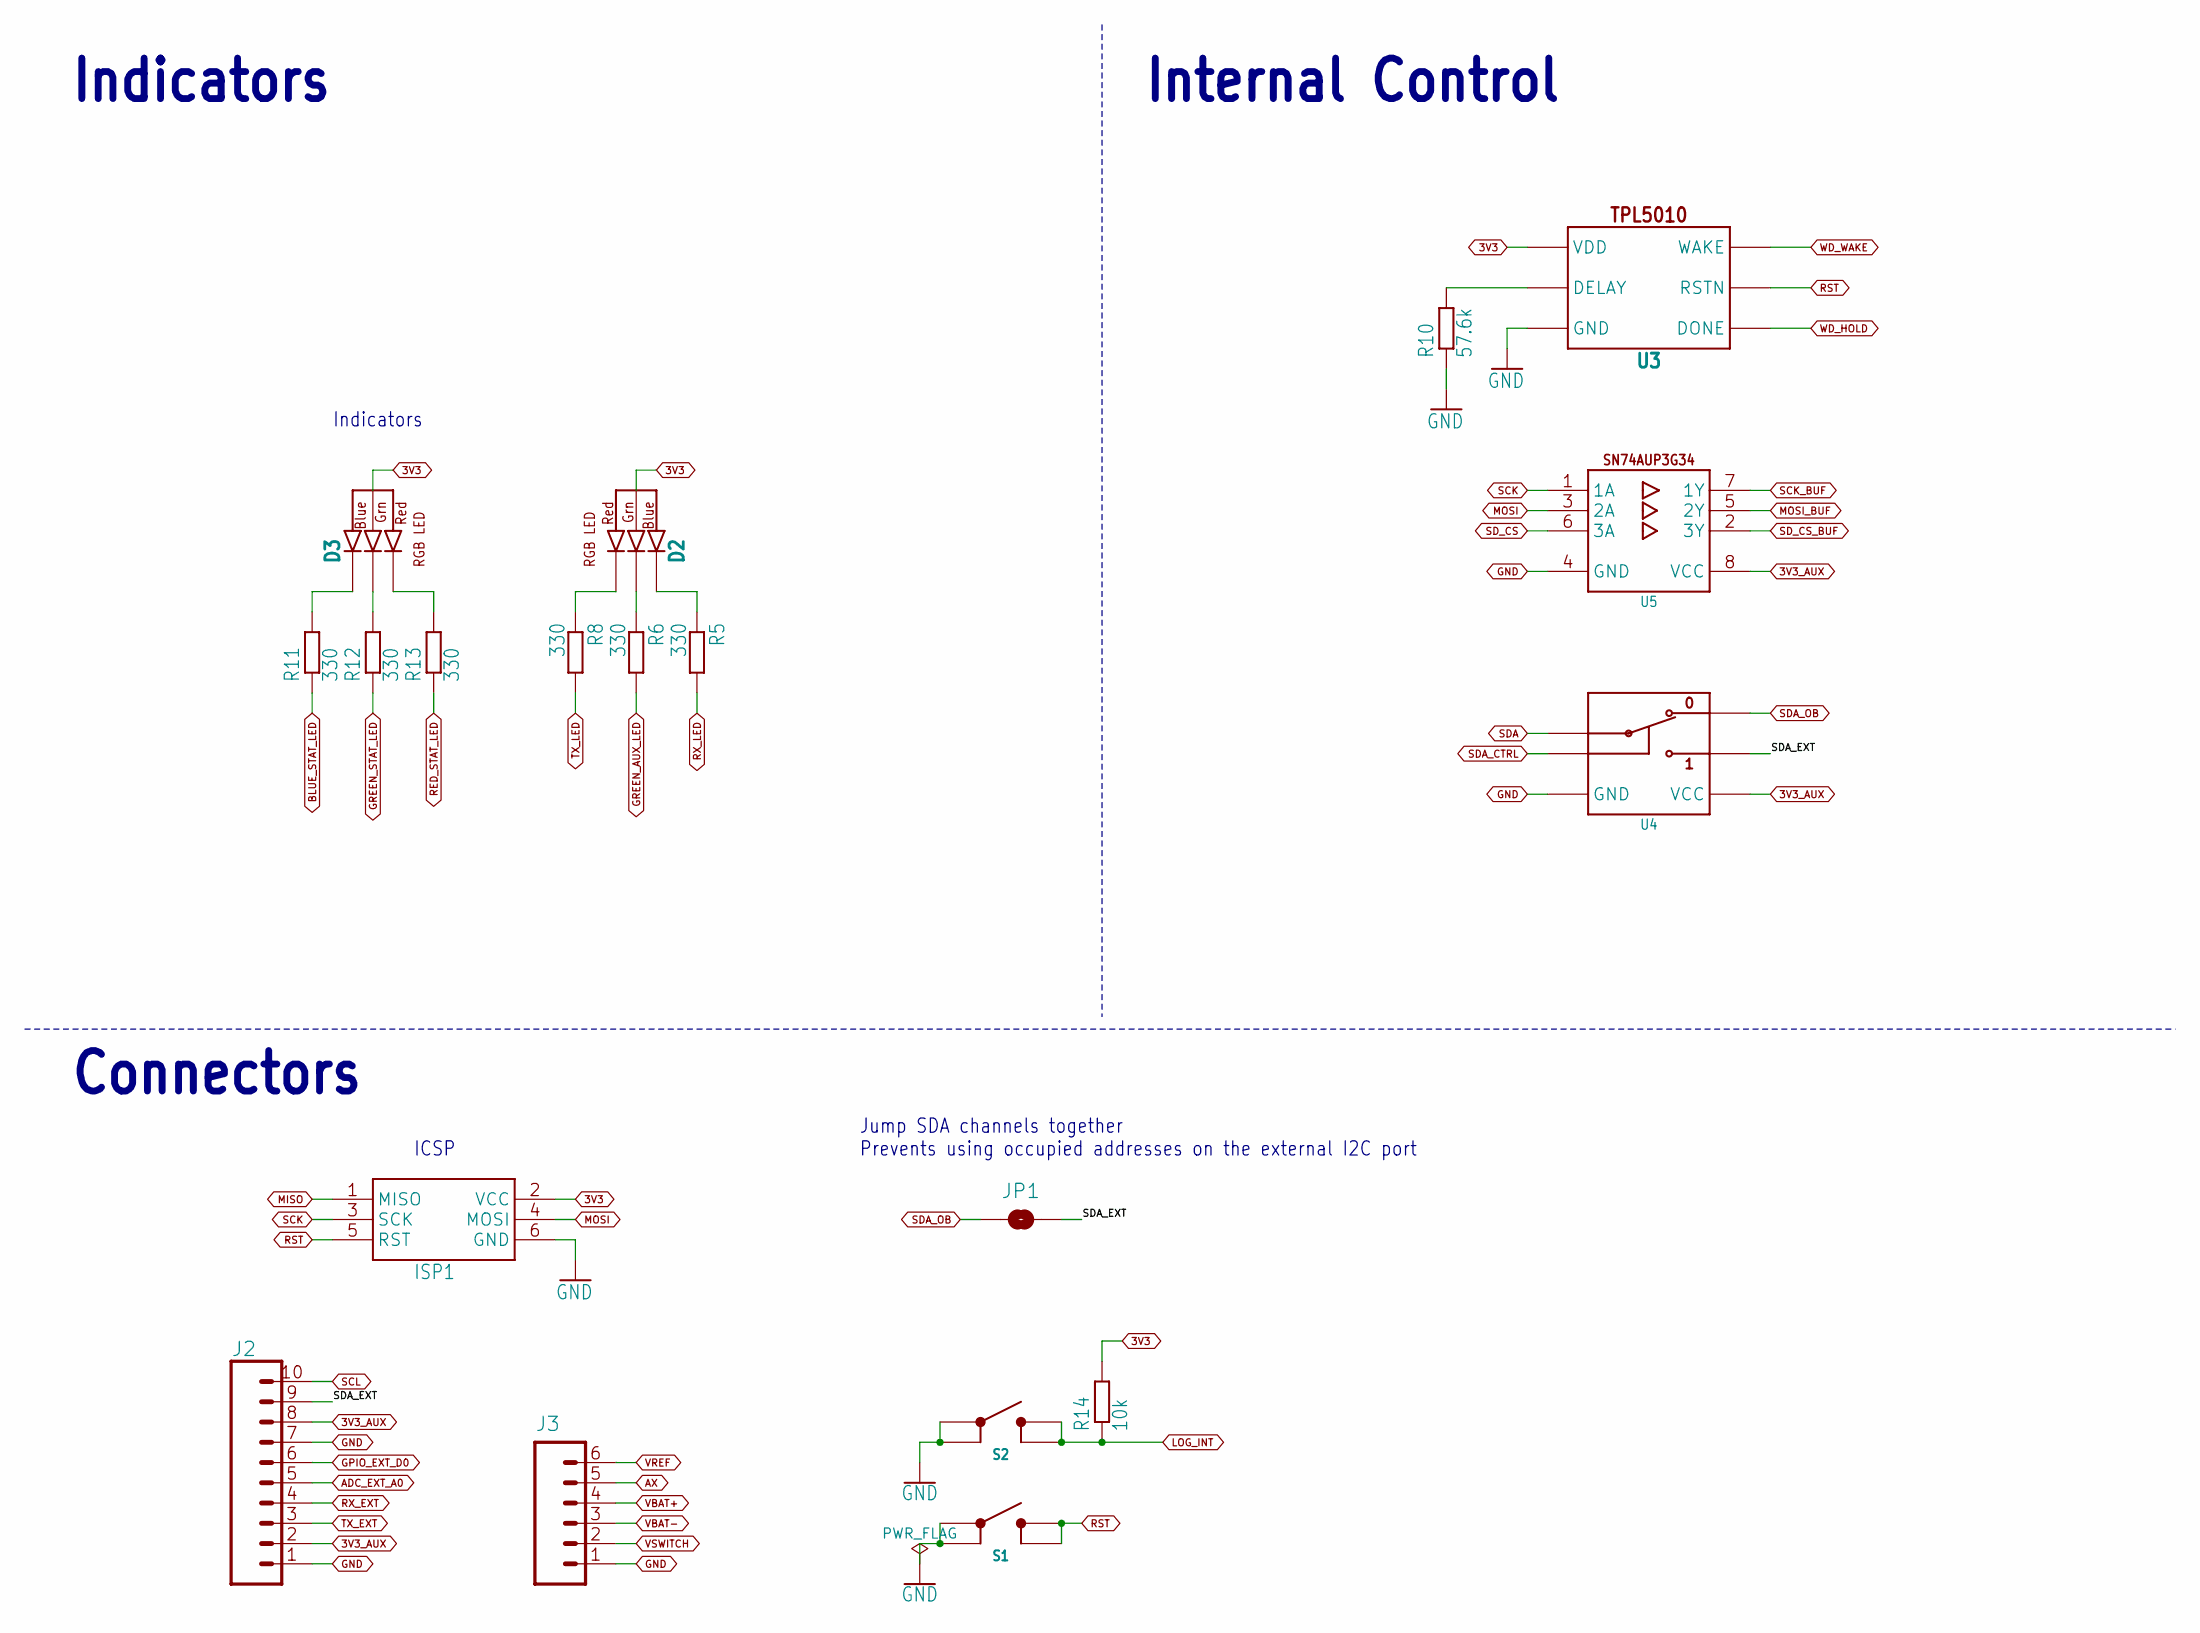
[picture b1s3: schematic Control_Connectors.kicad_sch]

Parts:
D2, D3: CLVBA-FKA; MPN CLVBA-FKA-CAEDH8BBB7A363; DIGIKEY CLVBA-FKA-CAEDH8BBB7A363CT-ND
ISP1: AVRISP-6; AVRISP; MPN 67997-206HLF; DIGIKEY 609-3234-ND
J2: CONN_102.54_SCREW; 1X10_SCREW_2.54_D1.1; MPN 1725737; DIGIKEY ED10567-ND
J3: CONN_6SCREW_2.54; 1X06_SCREW_2.54_D1.1; MPN 1725698; DIGIKEY ED10565-ND
JP1: JUMPER-SMT_2_NO_SILK; SMT-JUMPER_2_NO_SILK; MPN N/A; DIGIKEY DNP
R5, R6, R8, R11, R12, R13: 330; R0402; MPN ERJ-2RKF3300X; DIGIKEY P330LCT-ND
R10: 57.6k; R0603; MPN ERJ-3EKF5762V; DIGIKEY P57.6KHCT-ND
R14: 10k; R0402; MPN ERJ-2RKF1002X; DIGIKEY P10.0KLCT-ND
S1, S2: BUTTON4.2X3.2; SWITCH_4.2X3.2; MPN PTS810 SJG 250 SMTR LFS; DIGIKEY CKN10504CT-ND
U3: TPL5010DDC; DDC_R-PDSO-G6; MPN TPL5010QDDCRQ1; DIGIKEY 296-TPL5010QDDCRQ1CT-ND
U4: SN74LVC1G3157SC70; DCK_R-PDSO-G6; MPN SN74LVC1G3157DCKR; DIGIKEY 296-14909-1-ND
U5: SN74AUP3G34DCU; DCU_(R-PDSO-G8); MPN SN74AUP3G34DCUR; DIGIKEY 296-25595-1-ND

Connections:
3V3: D2.2 (ANODE), D3.2 (ANODE), ISP1.2 (VCC), R14.2, U3.1 (VDD); also elsewhere on the board
3V3_AUX: J2.2, J2.8, U4.5 (VCC), U5.8 (VCC); also elsewhere on the board
/Control_Connectors/SDA_EXT: J2.9, JP1.2, U4.1 (B2)
ADC_EXT_A0: J2.5; also elsewhere on the board
AX: J3.5; also elsewhere on the board
BLUE_STAT_LED: R11.1; also elsewhere on the board
GND: ISP1.6 (GND), J2.1, J2.7, J3.1, R10.1, S1.1, S1.2, S2.1, S2.2, U3.2 (GND), U4.2 (GND), U5.4 (GND); also elsewhere on the board
GPIO_EXT_D0: J2.6; also elsewhere on the board
GREEN_AUX_LED: R6.2; also elsewhere on the board
GREEN_STAT_LED: R12.1; also elsewhere on the board
LOG_INT: R14.1, S2.3 (4), S2.4 (3); also elsewhere on the board
MISO: ISP1.1 (MISO); also elsewhere on the board
MOSI: ISP1.4 (MOSI), U5.3 (2A); also elsewhere on the board
MOSI_BUF: U5.5 (2Y); also elsewhere on the board
unnamed: D2.3 (BLUE_CATH), R5.1
unnamed: D2.4 (GREEN_CATH), R6.1
unnamed: D2.1 (RED_CATH), R8.1
unnamed: D3.3 (BLUE_CATH), R11.2
unnamed: D3.4 (GREEN_CATH), R12.2
unnamed: D3.1 (RED_CATH), R13.2
unnamed: R10.2, U3.3 (DELAY)
RED_STAT_LED: R13.1; also elsewhere on the board
RST: ISP1.5 (RST), S1.3 (4), S1.4 (3), U3.6 (RSTN); also elsewhere on the board
RX_EXT: J2.4; also elsewhere on the board
RX_LED: R5.2; also elsewhere on the board
SCK: ISP1.3 (SCK), U5.1 (1A); also elsewhere on the board
SCK_BUF: U5.7 (1Y); also elsewhere on the board
SCL: J2.10; also elsewhere on the board
SDA: U4.4 (A); also elsewhere on the board
SDA_CTRL: U4.6 (S); also elsewhere on the board
SDA_OB: JP1.1, U4.3 (B1); also elsewhere on the board
SD_CS: U5.6 (3A); also elsewhere on the board
SD_CS_BUF: U5.2 (3Y); also elsewhere on the board
TX_EXT: J2.3; also elsewhere on the board
TX_LED: R8.2; also elsewhere on the board
VBAT+: J3.4; also elsewhere on the board
VBAT-: J3.3; also elsewhere on the board
VREF: J3.6; also elsewhere on the board
VSWITCH: J3.2; also elsewhere on the board
WD_HOLD: U3.4 (DONE); also elsewhere on the board

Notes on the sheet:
Jump SDA channels together Prevents using occupied addresses on the external I2C port
ICSP
Indicators
Internal Control
Connectors

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

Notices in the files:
README.md:
Hardware and documentation are licensed under a Creative Commons Attribution-ShareAlike 4.0 International License. Software in the Software/ directory is licensed under the GNU General Public License v3.
